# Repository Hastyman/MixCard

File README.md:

# MixCard
Three channel synth mixer in convenient business card sized format.
Card was created as part of a series from creators participating in the
www.synthcard.com project.

This is my take on a Synth DIY mixer --
It's a mix circuit based 
on the NPN Transistor. Credit and thanks for
the original schematic goes to NJ Ramsden. 
Check out his Insta @Synthnerd

Schematics under /Synthcard_Mixer_KiCad and panel design under /Inkscape_Files

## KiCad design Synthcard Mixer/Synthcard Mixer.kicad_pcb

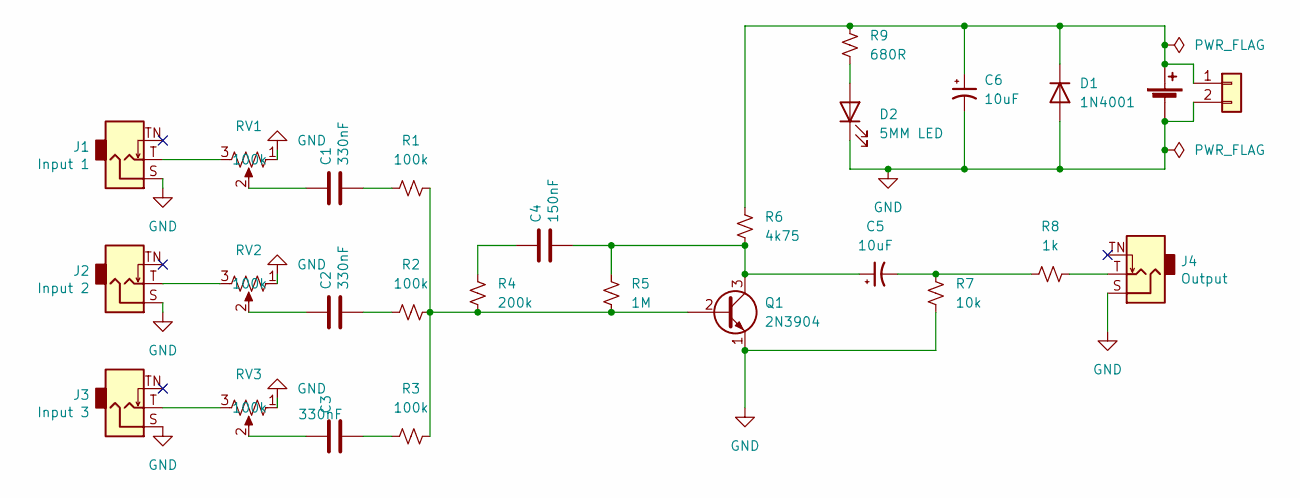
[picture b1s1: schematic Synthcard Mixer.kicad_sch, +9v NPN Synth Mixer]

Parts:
BT1: Battery_Cell
C1, C2, C3: 330nF; C_Rect_L7.0mm_W2.0mm_P5.00mm; Manufacturers Part Numb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 MMK5334K50J01L4BULK
C4: 150nF; C_Rect_L7.0mm_W2.0mm_P5.00mm; Manufacturers Part Numb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 MMK5154K50J01L4BULK
C5, C6: 10uF; CP_Radial_D5.0mm_P2.00mm
D1: 1N4001; D_DO-41_SOD81_P10.16mm_Horizontal
D2: 5MM LED; LED_D5.0mm
J1: Input 1; Jack_3.5mm_QingPu_WQP-PJ398SM_Vertical_CircularHoles; Manufacturers Part Numb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 PJ-3001F
J2: Input 2; Jack_3.5mm_QingPu_WQP-PJ398SM_Vertical_CircularHoles; Manufacturers Part Numb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 PJ-3001F
J3: Input 3; Jack_3.5mm_QingPu_WQP-PJ398SM_Vertical_CircularHoles; Manufacturers Part Numb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 PJ-3001F
J4: Output; Jack_3.5mm_QingPu_WQP-PJ398SM_Vertical_CircularHoles; Manufacturers Part Numb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 PJ-3001F
J5: Conn_01x02; PinHeader_1x02_P2.54mm_Vertical
Q1: 2N3904; TO-92L_HandSolder
R1, R2, R3: 100k; R_Axial_DIN0204_L3.6mm_D1.6mm_P5.08mm_Horizontal
R4: 200k; R_Axial_DIN0204_L3.6mm_D1.6mm_P5.08mm_Horizontal
R5: 1M; R_Axial_DIN0204_L3.6mm_D1.6mm_P5.08mm_Horizontal
R6: 4k75; R_Axial_DIN0204_L3.6mm_D1.6mm_P5.08mm_Horizontal
R7: 10k; R_Axial_DIN0204_L3.6mm_D1.6mm_P5.08mm_Horizontal
R8: 1k; R_Axial_DIN0204_L3.6mm_D1.6mm_P5.08mm_Horizontal
R9: 680R; R_Axial_DIN0204_L3.6mm_D1.6mm_P5.08mm_Horizontal
RV1, RV2, RV3: 100k; Potentiometer_Alps_RK09K_Single_Vertical; Manufacturers Part Numb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 RV09AF-40-20K-A100K

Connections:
GND: BT1.2 (-), C6.2, D1.2 (A), D2.1 (K), J1.S, J2.S, J3.S, J4.S, J5.2, Q1.1 (E), R7.2, RV1.1, RV2.1, RV3.1
unnamed: BT1.1 (+), C6.1, D1.1 (K), J5.1, R6.1, R9.1
unnamed: C1.1, RV1.2
unnamed: C1.2, R1.1
unnamed: C2.1, RV2.2
unnamed: C2.2, R2.1
unnamed: C3.1, RV3.2
unnamed: C3.2, R3.1
unnamed: C4.1, R4.1
unnamed: C4.2, C5.1, Q1.3 (C), R5.1, R6.2
unnamed: C5.2, R7.1, R8.1
unnamed: D2.2 (A), R9.2
unnamed: J1.T, RV1.3
unnamed: J2.T, RV2.3
unnamed: J3.T, RV3.3
unnamed: J4.T, R8.2
unnamed: Q1.2 (B), R1.2, R2.2, R3.2, R4.2, R5.2

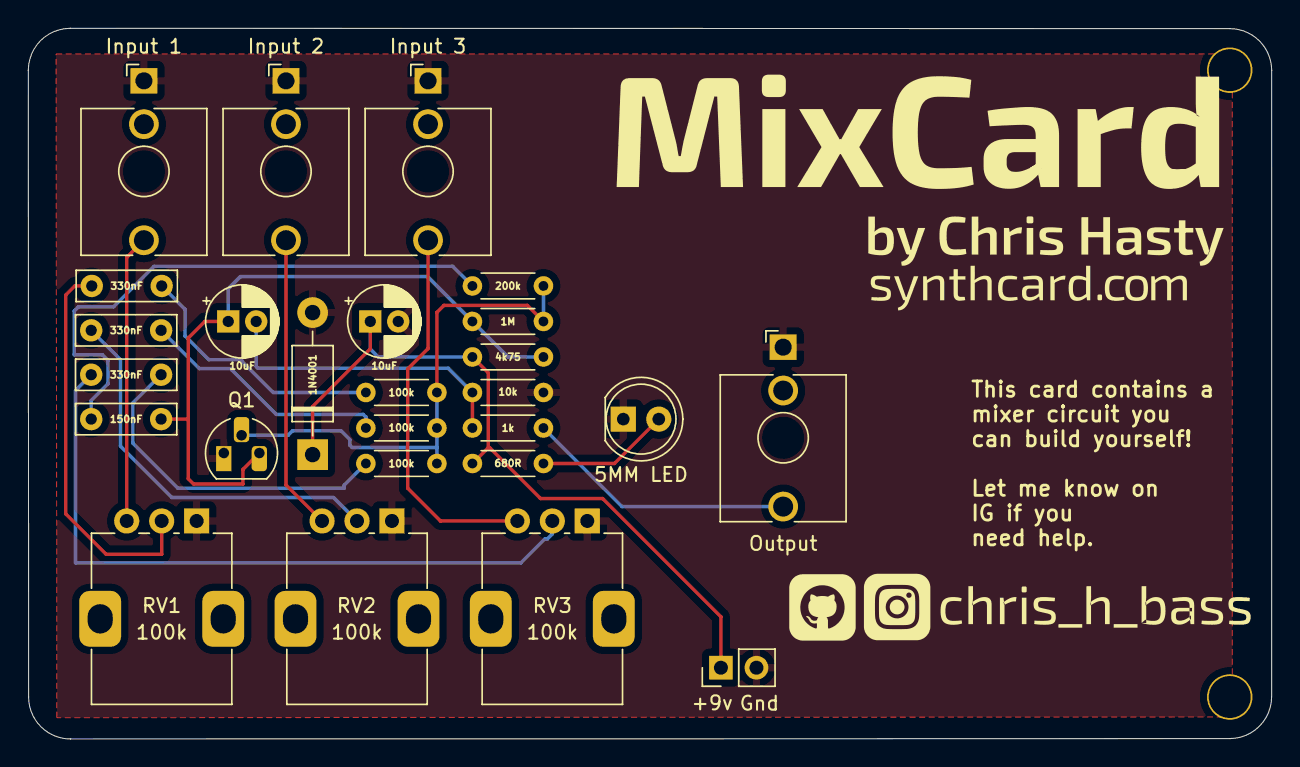
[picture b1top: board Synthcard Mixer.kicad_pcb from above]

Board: 2 copper layers, 88.9 x 50.8 mm, 26 parts (0 on the bottom side), 17 nets.

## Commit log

2022-11-27 Addition of KiCad files
2022-11-27 Inkscape Files added
2022-11-27 Imported BOM as CSV and PDF
